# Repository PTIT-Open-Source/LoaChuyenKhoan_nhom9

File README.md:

# esp32_loachuyenkhoan_prototype
 ESP32 PCB prototype with demo arduino code

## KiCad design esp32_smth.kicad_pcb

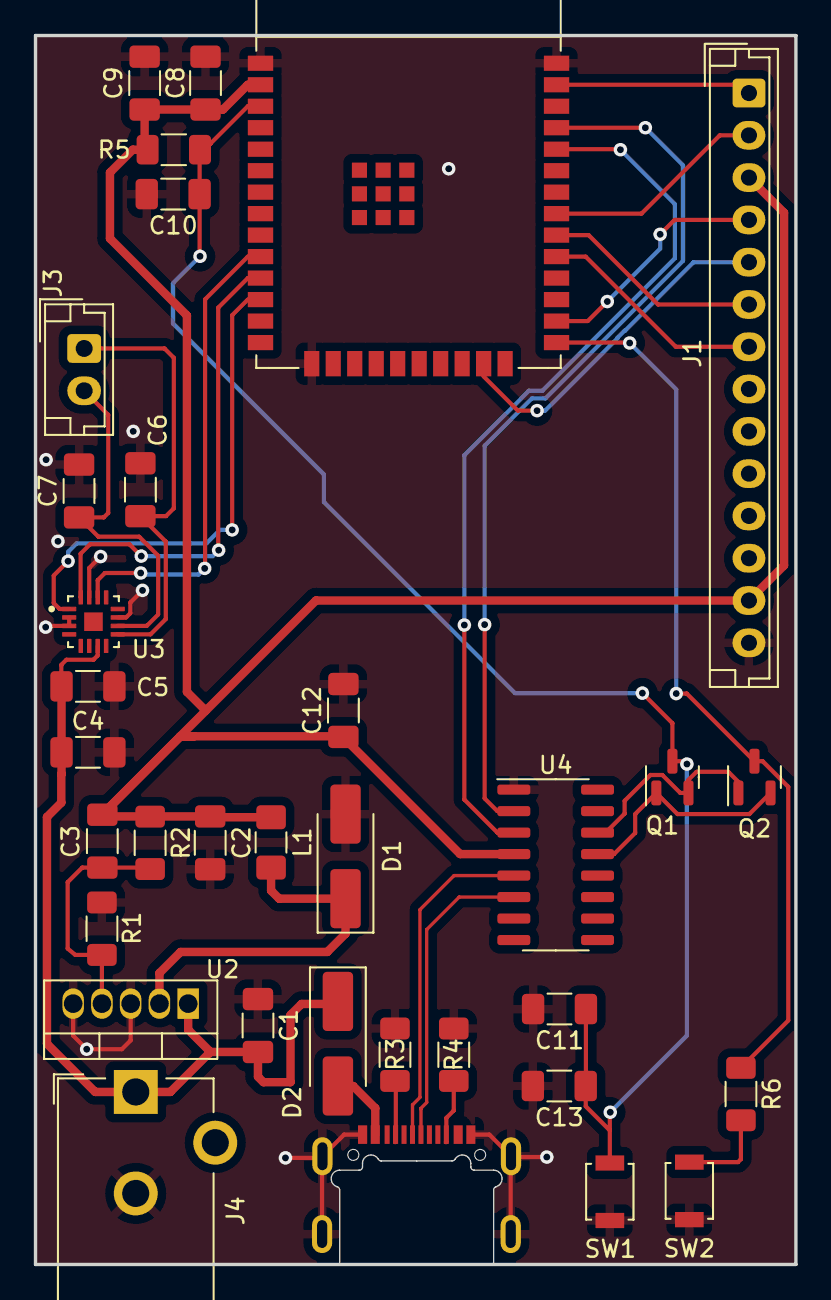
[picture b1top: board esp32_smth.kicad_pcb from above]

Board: 2 copper layers, 44.9 x 72.7 mm, 34 parts (0 on the bottom side), 28 nets.

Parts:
C1: 100uF; C_1206_3216Metric_Pad1.33x1.80mm_HandSolder
C2: 220uF; C_1206_3216Metric_Pad1.33x1.80mm_HandSolder
C3: 0.1pF; C_1206_3216Metric_Pad1.33x1.80mm_HandSolder
C4: 0.1u; C_1206_3216Metric_Pad1.33x1.80mm_HandSolder
C5: 10u; C_1206_3216Metric_Pad1.33x1.80mm_HandSolder
C6, C7: 220p; C_1206_3216Metric_Pad1.33x1.80mm_HandSolder
C8: 22uF; C_1206_3216Metric_Pad1.33x1.80mm_HandSolder
C9, C11, C12: 100nF; C_1206_3216Metric_Pad1.33x1.80mm_HandSolder
C10: 1pF; C_1206_3216Metric_Pad1.33x1.80mm_HandSolder
C13: 1uF; C_1206_3216Metric_Pad1.33x1.80mm_HandSolder
D1: 1N5822; D_SMA_Handsoldering
D2: SS110A; D_SMA_Handsoldering
J1: LCD + SD; JST_EH_B14B-EH-A_1x14_P2.50mm_Vertical
J2: USB_C_Receptacle_USB2.0; USB_C_Receptacle_HRO_TYPE-C-31-M-14
J3: SPEAKER; JST_EH_B2B-EH-A_1x02_P2.50mm_Vertical
J4: Barrel_Jack_MountingPin; BarrelJack_CUI_PJ-102AH_Horizontal
L1: 33uH; L_1206_3216Metric_Pad1.42x1.75mm_HandSolder
Q1, Q2: BSS138; SOT-23
R1: 1K; R_1206_3216Metric_Pad1.30x1.75mm_HandSolder
R2: 1.8K; R_1206_3216Metric_Pad1.30x1.75mm_HandSolder
R3, R4: 5.1K; R_1206_3216Metric_Pad1.30x1.75mm_HandSolder
R5: 10K; R_1206_3216Metric_Pad1.30x1.75mm_HandSolder
R6: 100R; R_1206_3216Metric_Pad1.30x1.75mm_HandSolder
SW1, SW2: SW_Push; SW_SPST_B3U-1000P
U1: ESP32-WROOM-E; ESP32-WROOM-32E
U2: LM2596T-ADJ; TO-220-5_Vertical
U3: MAX98357AETE_T; QFN50P300X300X80-17N
U4: CH340C; SOIC-16_3.9x9.9mm_P1.27mm

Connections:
BCLK: U1.11 (DAC_2/ADC2_CH9/GPIO26), U3.16 (BCLK)
BOOT: Q2.3 (D), R6.1, U1.25 (GPIO0/BOOT/ADC2_CH1)
CS: J1.7, U1.29 (GPIO5)
D+: J2.A6 (D+), J2.B6 (D+), U4.5 (UD+)
D-: J2.A7 (D-), J2.B7 (D-), U4.6 (UD-)
DC: J1.4, U1.26 (ADC2_CH0/GPIO4)
DIN: U1.12 (ADC2_CH7/GPIO27), U3.1 (DIN)
EN: C10.1, C11.1, C13.1, Q1.3 (D), R5.2, SW1.1, U1.3 (EN/CHIP_PU)
GND: C1.2, C2.2, C4.2, C5.2, C6.2, C7.2, C8.2, C9.2, C10.2, C11.2, C12.2, C13.2, D1.2 (A), J1.14, J2.A1 (GND), J2.A12 (GND), J2.B1 (GND), J2.B12 (GND), J2.S1 (SHIELD), J4.2, R1.2, R3.2, R4.2, SW1.2, SW2.2, U1.1 (GND), U1.15 (GND), U1.38 (GND), U2.3 (GND), U2.5 (~ON/OFF), U3.2 (GAIN_SLOT), U3.3 (GND), U3.11 (GND), U3.15 (GND), U4.1 (GND)
LRCLK: U1.10 (DAC_1/ADC2_CH8/GPIO25), U3.14 (LRCLK)
MISO: J1.2, U1.31 (GPIO19)
MOSI: J1.1, U1.37 (GPIO23)
unnamed: D1.1 (K), L1.1, U2.2 (OUT)
unnamed: D2.2 (A), J2.A4 (VBUS), J2.A9 (VBUS), J2.B4 (VBUS), J2.B9 (VBUS)
unnamed: J2.A5 (CC1), R3.1
unnamed: J2.B5 (CC2), R4.1
unnamed: C7.1, J3.2, U3.10 (OUTN)
unnamed: C6.1, J3.1, U3.9 (OUTP)
unnamed: Q1.1 (G), Q2.2 (S), U4.13 (~DTR)
unnamed: Q1.2 (S), Q2.1 (G), U4.14 (~RTS)
unnamed: R6.2, SW2.1
unnamed: C3.2, R1.1, R2.2, U2.4 (FB)
PWR: C2.1, C3.1, C8.1, C9.1, C12.1, J1.3, J1.13, L1.2, R2.1, R5.1, U1.2 (3V3), U4.4 (V3), U4.16 (VCC)
RESET: J1.5, U1.23 (MTDO/GPIO15/ADC2_CH3)
RX0: U1.34 (U0RXD/GPIO3), U4.3 (RXD)
SCLK: J1.6, U1.30 (GPIO18)
TX0: U1.35 (U0TXD/GPIO1), U4.2 (TXD)
VCC: C1.1, C4.1, C5.1, D2.1 (K), J4.1, U2.1 (VIN), U3.7 (VDD)
